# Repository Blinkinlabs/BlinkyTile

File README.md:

BlinkyTile: Build Your Own Dynamic Light Sculptures
==========

BlinkyTile is a very special type of pentagonal tile, designed to let you create your own custom light sculptures.

This is the source repository for the BlinkyTile design and software. For more information, head to:

http://blinkytile.com/

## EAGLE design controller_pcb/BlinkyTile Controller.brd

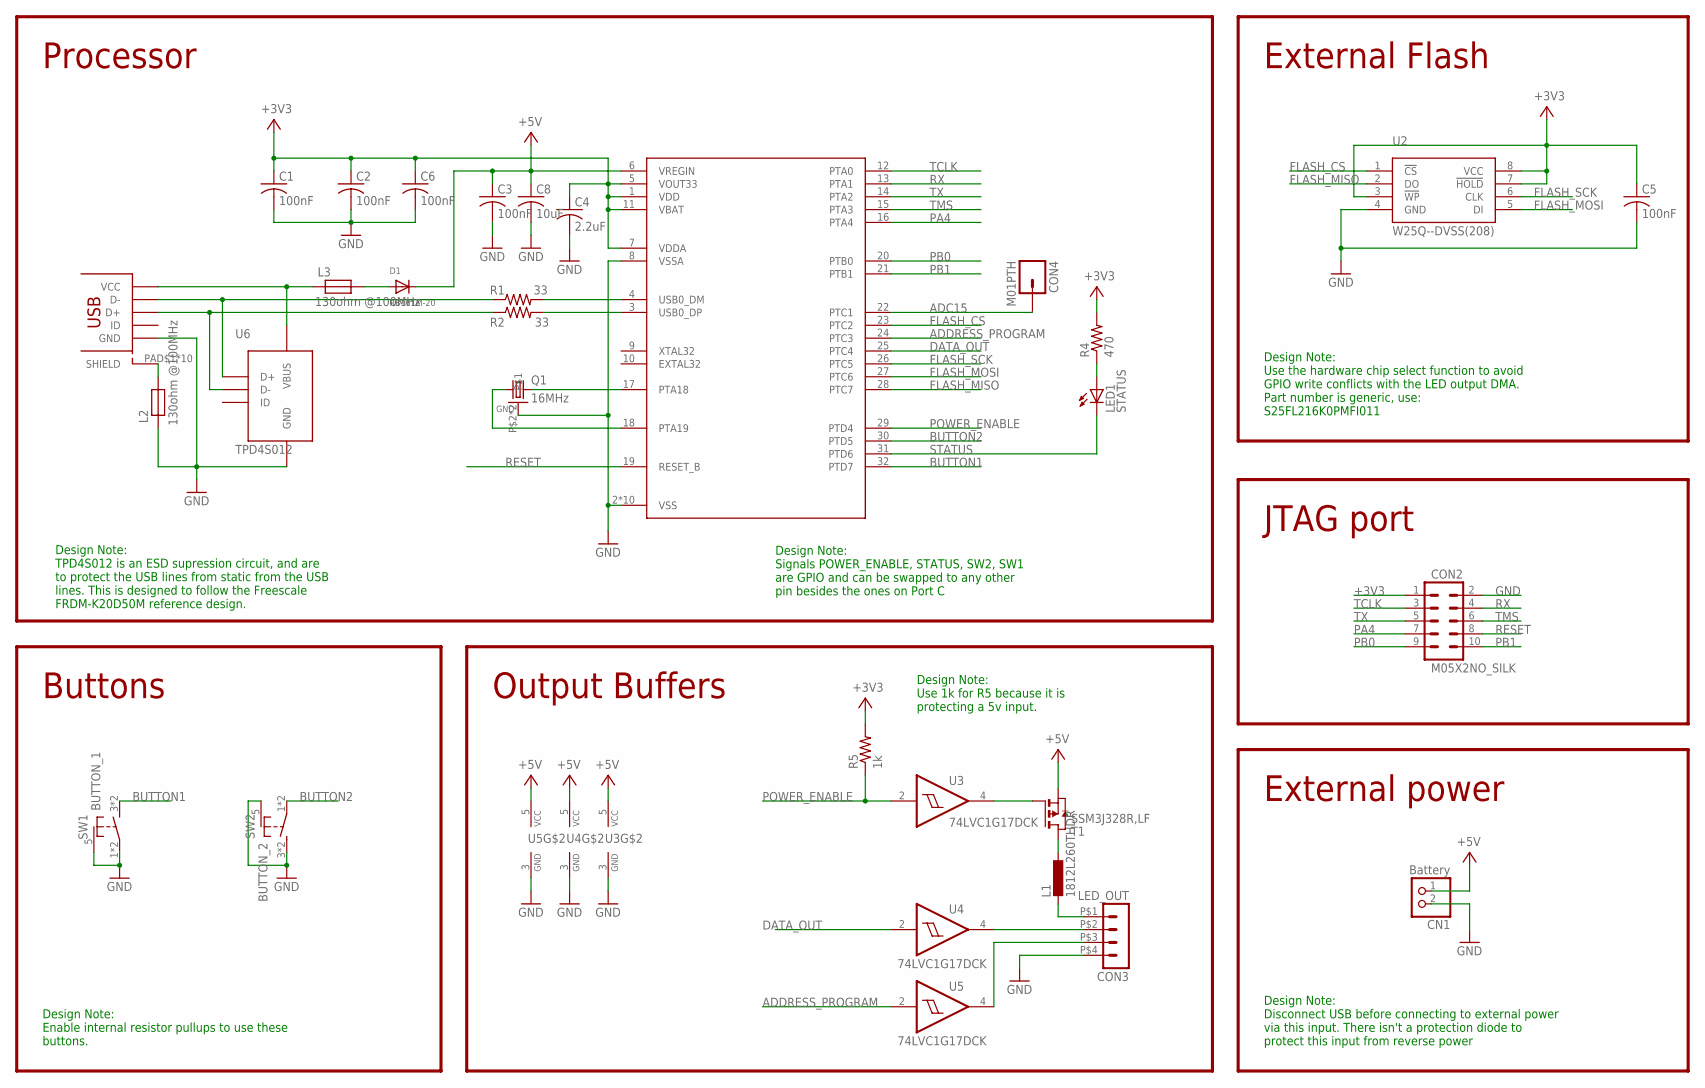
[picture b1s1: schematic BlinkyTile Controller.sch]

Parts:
C1, C2, C3, C5, C6: 100nF; C0402
C4: 2.2uF; C0402
C8: 10uF; C0805K
CN1: Battery; JST-PH-2-THM-RA
CON1: USB_MICROSMT+THRUHULE; USB_MICRO_THRUHOLE
CON2: M05X2NO_SILK; 2X5_NOSILK
CON3: LED_OUT; DUPONT-4P
CON4: M01PTH; 1X01
D1: RB161M-20; SOD-123
L1: 1812L260THDR; L1812
L2, L3: 130ohm @100MHz; 0805
LED1: STATUS; CHIPLED_0805
Q1: 16MHz; CRSYTAL_2520
R1, R2: 33; R0402
R4: 470; R0402
R5: 1k; R0402
SW1: BUTTON_1; TD-07XB
SW2: BUTTON_2; TD-07XB
T1: SSM3J328R,LF; SOT-23
U1: MK20D--VFM5; QFN32_5X5_LONGLEADS
U2: W25Q--DVSS(208); SOIC8-208
U3, U4, U5: 74LVC1G17DCK; SC70-5
U6: TPD4S012; R-PUSON-N6

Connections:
+3V3: C1.1, C2.1, C4.1, C5.1, C6.1, CON2.1, R4.2, R5.2, U1.1 (VDD), U1.5 (VOUT33), U1.7 (VDDA), U1.11 (VBAT), U2.3 (!WP), U2.7 (!HOLD), U2.8 (VCC)
+5V: C3.1, C8.1, CN1.1 (2), D1.C, T1.2 (S), U1.6 (VREGIN), U3.5 (VCC), U4.5 (VCC), U5.5 (VCC)
ADC15: CON4.1, U1.22 (PTC1)
ADDRESS_PROGRAM: U1.24 (PTC3), U5.2 (I)
BUTTON1: SW1.3 (S), SW1.4 (S), U1.32 (PTD7)
BUTTON2: SW2.1, SW2.2, U1.30 (PTD5)
DATA_OUT: U1.25 (PTC4), U4.2 (I)
FLASH_CS: U1.23 (PTC2), U2.1 (!CS)
FLASH_MISO: U1.28 (PTC7), U2.2 (DO)
FLASH_MOSI: U1.27 (PTC6), U2.5 (DI)
FLASH_SCK: U1.26 (PTC5), U2.6 (CLK)
GND: C1.2, C2.2, C3.2, C4.2, C5.2, C6.2, C8.2, CN1.2 (1), CON1.PIN$5 (GND), CON2.2, CON3.P$4 (4), L2.2, Q1.P$2, Q1.P$4, SW1.1, SW1.2, SW1.5 (SHIELD), SW2.3 (S), SW2.4 (S), SW2.5 (SHIELD), U1.2 (VSS), U1.8 (VSSA), U1.PAD@1 (VSS), U1.PAD@2 (VSS), U1.PAD@3 (VSS), U1.PAD@4 (VSS), U1.PAD@5 (VSS), U1.PAD@6 (VSS), U1.PAD@9 (VSS), U1.PAD@10 (VSS), U1.PAD@11 (VSS), U2.4 (GND), U3.3 (GND), U4.3 (GND), U5.3 (GND), U6.P$4 (GND)
LED_DATA: CON3.P$2 (2), U4.4 (O)
unnamed: Q1.P$1 (1), U1.18 (PTA19)
unnamed: Q1.P$3 (2), U1.17 (PTA18)
unnamed: CON1.PIN$1 (VCC), L3.2, U6.P$6 (VBUS)
unnamed: CON3.P$3 (3), U5.4 (O)
unnamed: L1.1, T1.1 (D)
unnamed: T1.3 (G), U3.4 (O)
unnamed: CON1.PIN$2 (D-), R1.1, U6.P$1 (D+)
unnamed: CON3.P$1 (1), L1.2
unnamed: D1.A, L3.1
unnamed: CON1.PIN$3 (D+), R2.1, U6.P$2 (D-)
unnamed: R1.2, U1.4 (USB0_DM)
unnamed: R2.2, U1.3 (USB0_DP)
unnamed: LED1.A, R4.1
PA4: CON2.7, U1.16 (PTA4)
PB0: CON2.9, U1.20 (PTB0)
PB1: CON2.10, U1.21 (PTB1)
POWER_ENABLE: R5.1, U1.29 (PTD4), U3.2 (I)
RESET: CON2.8, U1.19 (RESET_B)
RX: CON2.4, U1.13 (PTA1)
SHIELD: CON1.PAD$1 (SHIELD), CON1.PAD$2 (SHIELD), CON1.PAD$3 (SHIELD), CON1.PAD$4 (SHIELD), CON1.PAD$5 (SHIELD), CON1.PAD$6 (SHIELD), CON1.PAD$7 (SHIELD), CON1.PAD$8 (SHIELD), CON1.PAD$9 (SHIELD), CON1.PAD$10 (SHIELD), L2.1
STATUS: LED1.C, U1.31 (PTD6)
TCLK: CON2.3, U1.12 (PTA0)
TMS: CON2.6, U1.15 (PTA3)
TX: CON2.5, U1.14 (PTA2)

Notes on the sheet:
Processor
External Flash
Buttons
Design Note: Signals POWER_ENABLE, STATUS, SW2, SW1 are GPIO and can be swapped to any other pin besides the ones on Port C
Design Note: TPD4S012 is an ESD supression circuit, and are to protect the USB lines from static from the USB lines. This is designed to follow the Freescale FRDM-K20D50M reference design.
Output Buffers
JTAG port
External power
Design Note: Use 1k for R5 because it is protecting a 5v input.
Design Note: Use the hardware chip select function to avoid GPIO write conflicts with the LED output DMA. Part number is generic, use: S25FL216K0PMFI011
Design Note: Disconnect USB before connecting to external power via this input. There isn't a protection diode to protect this input from reverse power
Design Note: Enable internal resistor pullups to use these buttons.

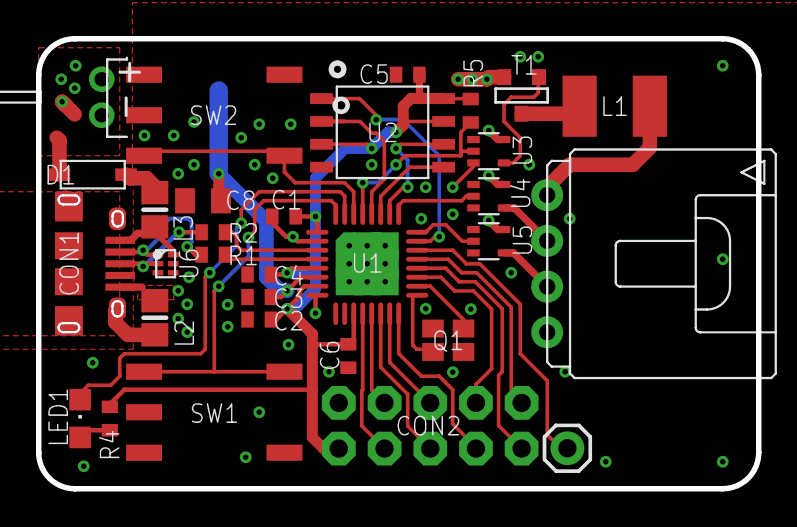
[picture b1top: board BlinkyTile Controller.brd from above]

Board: 2 copper layers, 40.0 x 25.0 mm, 31 parts (0 on the bottom side), 37 nets.

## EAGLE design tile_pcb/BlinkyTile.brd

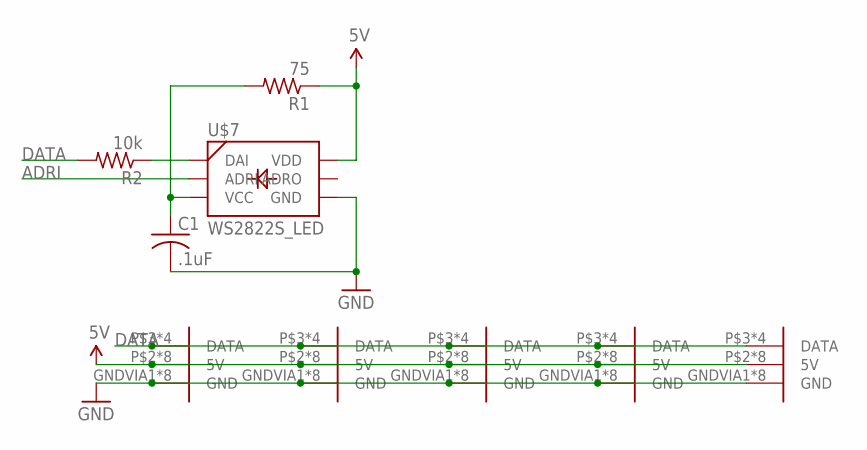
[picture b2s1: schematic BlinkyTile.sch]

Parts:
C1: .1uF; C0603
R1: 75; R0603
R2: 10k; R0603
U$2, U$3, U$4, U$5, U$6: D_EDGEMOD; D_EDGE_SLOT_MOD
U$7: WS2822S_LED

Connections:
5V: R1.1, U$2.P$2 (5V), U$2.P$4 (5V), U$2.P$7 (5V), U$2.P$9 (5V), U$2.PWRVIA1 (5V), U$2.PWRVIA3 (5V), U$2.PWRVIA4 (5V), U$2.PWRVIA6 (5V), U$3.P$2 (5V), U$3.P$4 (5V), U$3.P$7 (5V), U$3.P$9 (5V), U$3.PWRVIA1 (5V), U$3.PWRVIA3 (5V), U$3.PWRVIA4 (5V), U$3.PWRVIA6 (5V), U$4.P$2 (5V), U$4.P$4 (5V), U$4.P$7 (5V), U$4.P$9 (5V), U$4.PWRVIA1 (5V), U$4.PWRVIA3 (5V), U$4.PWRVIA4 (5V), U$4.PWRVIA6 (5V), U$5.P$2 (5V), U$5.P$4 (5V), U$5.P$7 (5V), U$5.P$9 (5V), U$5.PWRVIA1 (5V), U$5.PWRVIA3 (5V), U$5.PWRVIA4 (5V), U$5.PWRVIA6 (5V), U$6.P$2 (5V), U$6.P$4 (5V), U$6.P$7 (5V), U$6.P$9 (5V), U$6.PWRVIA1 (5V), U$6.PWRVIA3 (5V), U$6.PWRVIA4 (5V), U$6.PWRVIA6 (5V), U$7.6 (VDD)
ADRI: U$7.2 (ADRI)
DATA: R2.2, U$2.P$3 (DATA), U$2.P$8 (DATA), U$2.SIGVIA1 (DATA), U$2.SIGVIA3 (DATA), U$3.P$3 (DATA), U$3.P$8 (DATA), U$3.SIGVIA1 (DATA), U$3.SIGVIA3 (DATA), U$4.P$3 (DATA), U$4.P$8 (DATA), U$4.SIGVIA1 (DATA), U$4.SIGVIA3 (DATA), U$5.P$3 (DATA), U$5.P$8 (DATA), U$5.SIGVIA1 (DATA), U$5.SIGVIA3 (DATA), U$6.P$3 (DATA), U$6.P$8 (DATA), U$6.SIGVIA1 (DATA), U$6.SIGVIA3 (DATA)
GND: C1.2, U$2.GNDVIA1 (GND), U$2.GNDVIA3 (GND), U$2.GNDVIA4 (GND), U$2.GNDVIA6 (GND), U$2.P$1 (GND), U$2.P$5 (GND), U$2.P$6 (GND), U$2.P$10 (GND), U$3.GNDVIA1 (GND), U$3.GNDVIA3 (GND), U$3.GNDVIA4 (GND), U$3.GNDVIA6 (GND), U$3.P$1 (GND), U$3.P$5 (GND), U$3.P$6 (GND), U$3.P$10 (GND), U$4.GNDVIA1 (GND), U$4.GNDVIA3 (GND), U$4.GNDVIA4 (GND), U$4.GNDVIA6 (GND), U$4.P$1 (GND), U$4.P$5 (GND), U$4.P$6 (GND), U$4.P$10 (GND), U$5.GNDVIA1 (GND), U$5.GNDVIA3 (GND), U$5.GNDVIA4 (GND), U$5.GNDVIA6 (GND), U$5.P$1 (GND), U$5.P$5 (GND), U$5.P$6 (GND), U$5.P$10 (GND), U$6.GNDVIA1 (GND), U$6.GNDVIA3 (GND), U$6.GNDVIA4 (GND), U$6.GNDVIA6 (GND), U$6.P$1 (GND), U$6.P$5 (GND), U$6.P$6 (GND), U$6.P$10 (GND), U$7.4 (GND)
unnamed: C1.1, R1.2, U$7.3 (VCC)
unnamed: R2.1, U$7.1 (DAI)

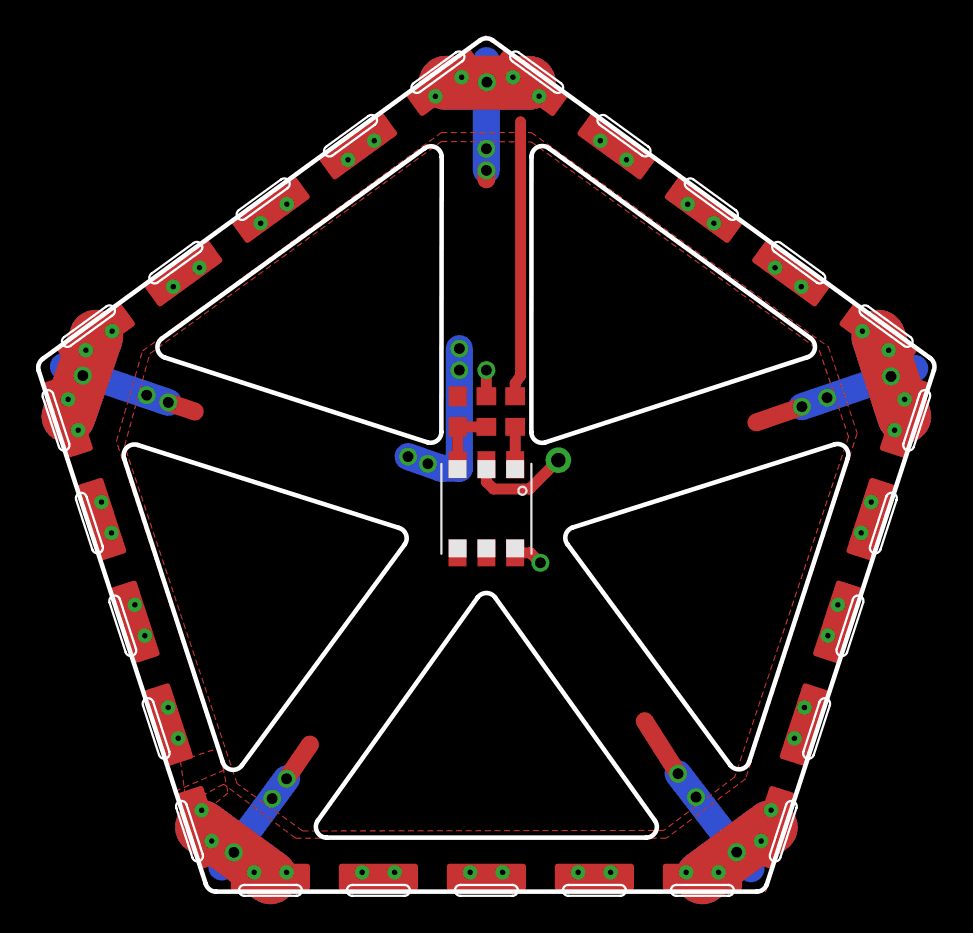
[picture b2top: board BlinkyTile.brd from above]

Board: 2 copper layers, 49.8 x 47.6 mm, 9 parts (0 on the bottom side), 5 nets.

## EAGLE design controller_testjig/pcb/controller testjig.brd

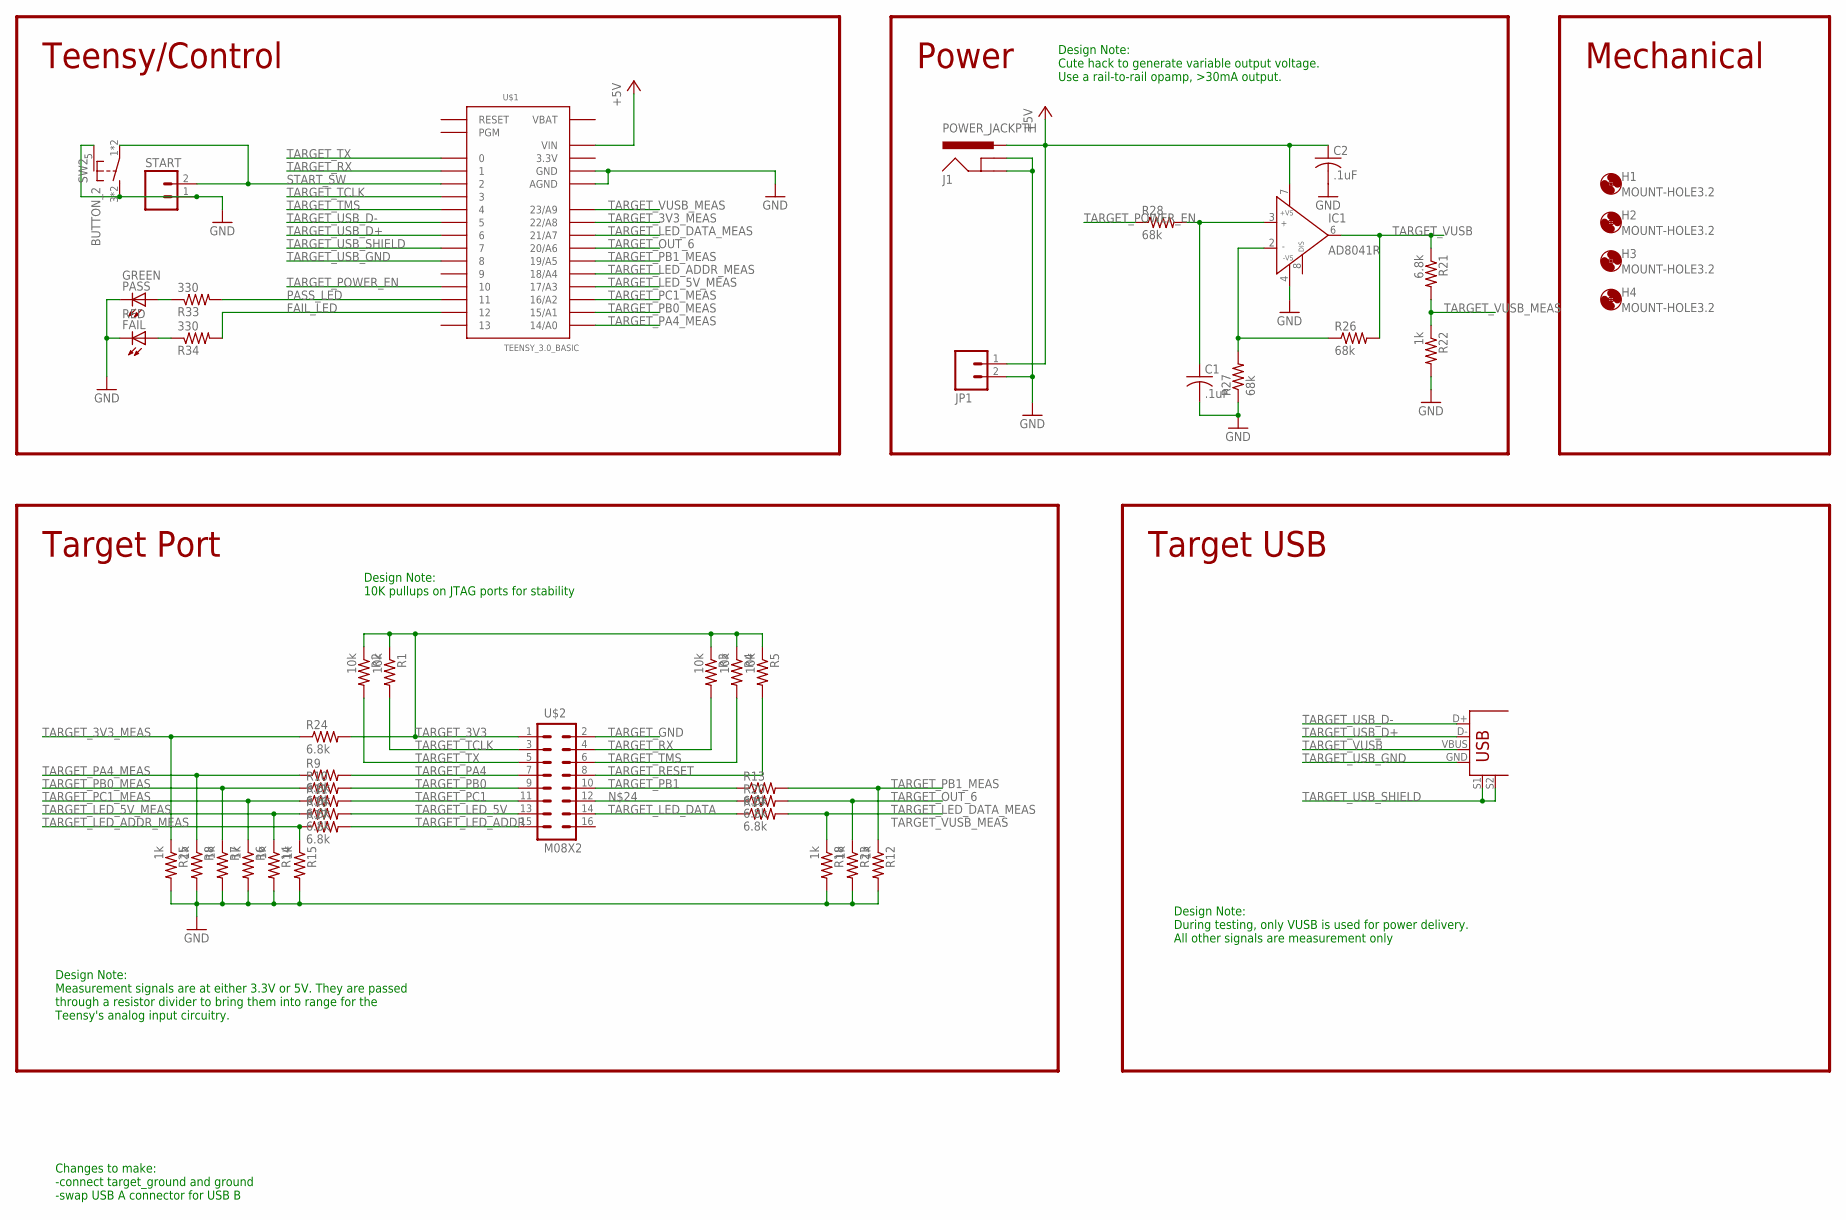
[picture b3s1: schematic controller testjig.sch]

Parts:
C1, C2: .1uF; C0603
FAIL: RED; LED5MM
H1, H2, H3, H4: MOUNT-HOLE3.2; 3,2
IC1: AD8041R; SO8
J1: POWER_JACKPTH; POWER_JACK_PTH
JP1: M023.5MM; SCREWTERMINAL-3.5MM-2
PASS: GREEN; LED5MM
R1, R2, R3, R4, R5: 10k; R0603
R6, R7, R8, R12, R14, R15, R18, R22, R23, R25: 1k; R0603
R9, R10, R11, R13, R16, R17, R19, R20, R21, R24: 6.8k; R0603
R26, R27, R28: 68k; R0603
R33, R34: 330; R0603
START: M02; 02P
SW2: BUTTON_2; TD-07XB
U$1: TEENSY_3.0_BASIC
U$2: M08X2; 2X8
U$3: USB+SHIELD; USB-B-PTH

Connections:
3.3V: U$1.3.3V, U$1.3.3V1 (3.3V)
+5V: C2.1, IC1.7 (+VS), J1.PWR, JP1.1, U$1.VIN
FAIL_LED: R34.2, U$1.12
GND: C1.2, C2.2, FAIL.K (C), IC1.4 (-VS), J1.GND, J1.GNDBREAK, JP1.2, PASS.K (C), R6.2, R7.2, R8.2, R12.2, R14.2, R15.2, R18.2, R22.2, R23.2, R25.2, R27.1, START.1, SW2.3 (S), SW2.4 (S), SW2.5 (SHIELD), U$1.AGND, U$1.GND, U$1.GND1 (GND)
GOOD: PASS.A, R33.1
unnamed: IC1.2 (IN-), R26.1, R27.2
unnamed: C1.1, IC1.3 (IN+), R28.2
unnamed: R20.1, U$2.12
unnamed: FAIL.A, R34.1
PASS_LED: R33.2, U$1.11
START_SW: START.2, SW2.1, SW2.2, U$1.2
TARGET_3V3: R1.1, R2.1, R3.1, R4.1, R5.1, R24.2, U$2.1
TARGET_3V3_MEAS: R24.1, R25.1, U$1.22/A8
TARGET_GND: U$2.2
TARGET_LED_5V: R16.2, U$2.13
TARGET_LED_5V_MEAS: R14.1, R16.1, U$1.17/A3
TARGET_LED_ADDR: R17.2, U$2.15
TARGET_LED_ADDR_MEAS: R15.1, R17.1, U$1.18/A4
TARGET_LED_DATA: R19.1, U$2.14
TARGET_LED_DATA_MEAS: R18.1, R19.2, U$1.21/A7
TARGET_OUT_6: R20.2, R23.1, U$1.20/A6
TARGET_PA4: R9.2, U$2.7
TARGET_PA4_MEAS: R8.1, R9.1, U$1.14/A0
TARGET_PB0: R10.2, U$2.9
TARGET_PB0_MEAS: R7.1, R10.1, U$1.15/A1
TARGET_PB1: R13.1, U$2.10
TARGET_PB1_MEAS: R12.1, R13.2, U$1.19/A5
TARGET_PC1: R11.2, U$2.11
TARGET_PC1_MEAS: R6.1, R11.1, U$1.16/A2
TARGET_POWER_EN: R28.1, U$1.10
TARGET_RESET: R5.2, U$2.8
TARGET_RX: R3.2, U$1.1, U$2.4
TARGET_TCLK: R1.2, U$1.3, U$2.3
TARGET_TMS: R4.2, U$1.4, U$2.6
TARGET_TX: R2.2, U$1.0, U$2.5
TARGET_USB_D+: U$1.5, U$3.D+
TARGET_USB_D-: U$1.6, U$3.D-
TARGET_USB_GND: U$1.8, U$3.GND
TARGET_USB_SHIELD: U$1.7, U$3.S1, U$3.S2
TARGET_VUSB: IC1.6 (OUT), R21.1, R26.2, U$3.VBUS
TARGET_VUSB_MEAS: R21.2, R22.1, U$1.23/A9
VBAT: U$1.VBAT

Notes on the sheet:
Teensy/Control
Target Port
Design Note: Measurement signals are at either 3.3V or 5V. They are passed through a resistor divider to bring them into range for the Teensy's analog input circuitry.
Design Note: 10K pullups on JTAG ports for stability
Mechanical
Target USB
Power
Design Note: During testing, only VUSB is used for power delivery. All other signals are measurement only
Design Note: Cute hack to generate variable output voltage. Use a rail-to-rail opamp, >30mA output.
Changes to make: -connect target_ground and ground -swap USB A connector for USB B

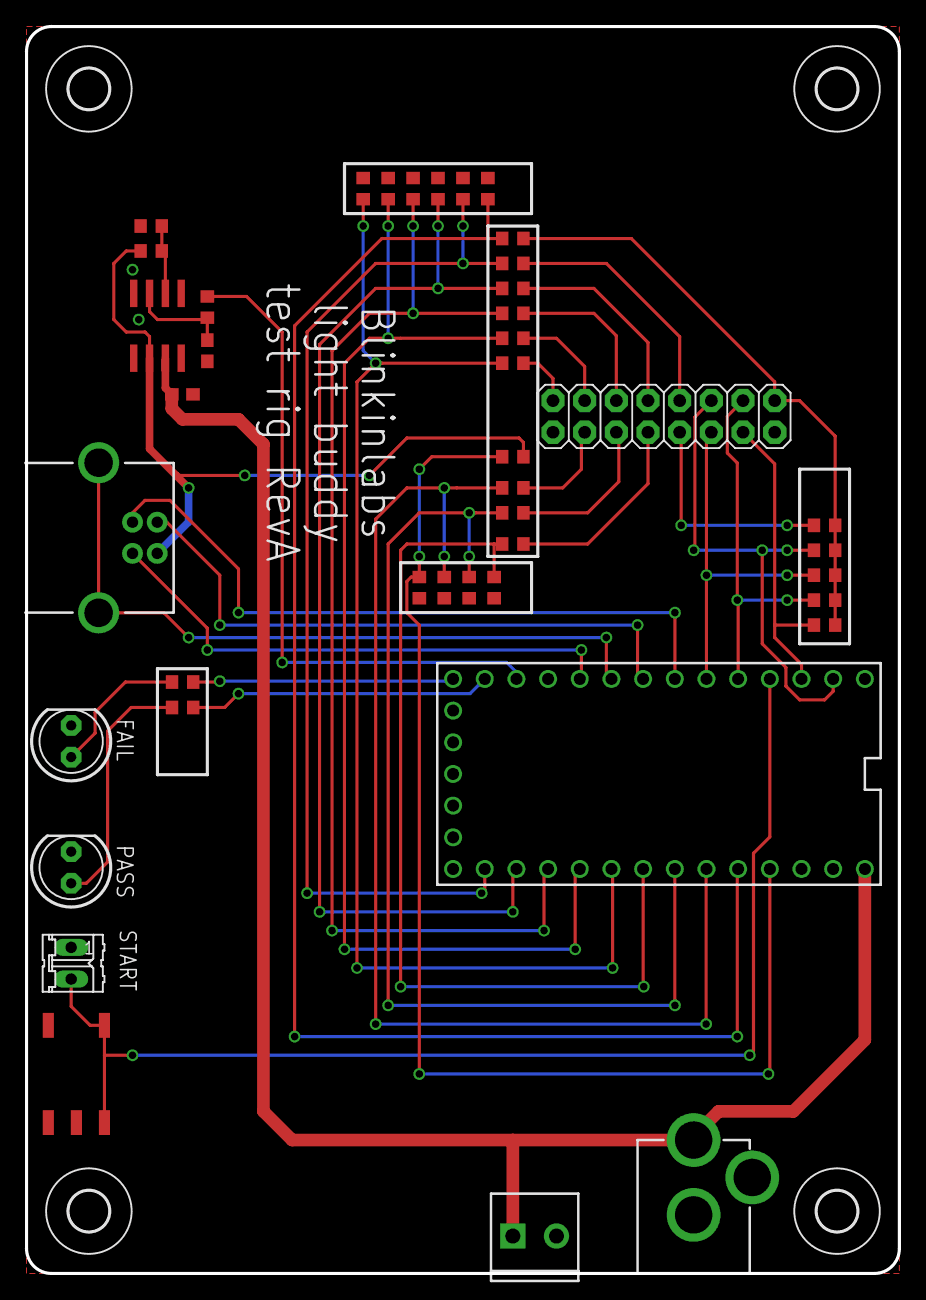
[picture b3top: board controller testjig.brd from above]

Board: 2 copper layers, 70.0 x 100.0 mm, 46 parts (0 on the bottom side), 40 nets.

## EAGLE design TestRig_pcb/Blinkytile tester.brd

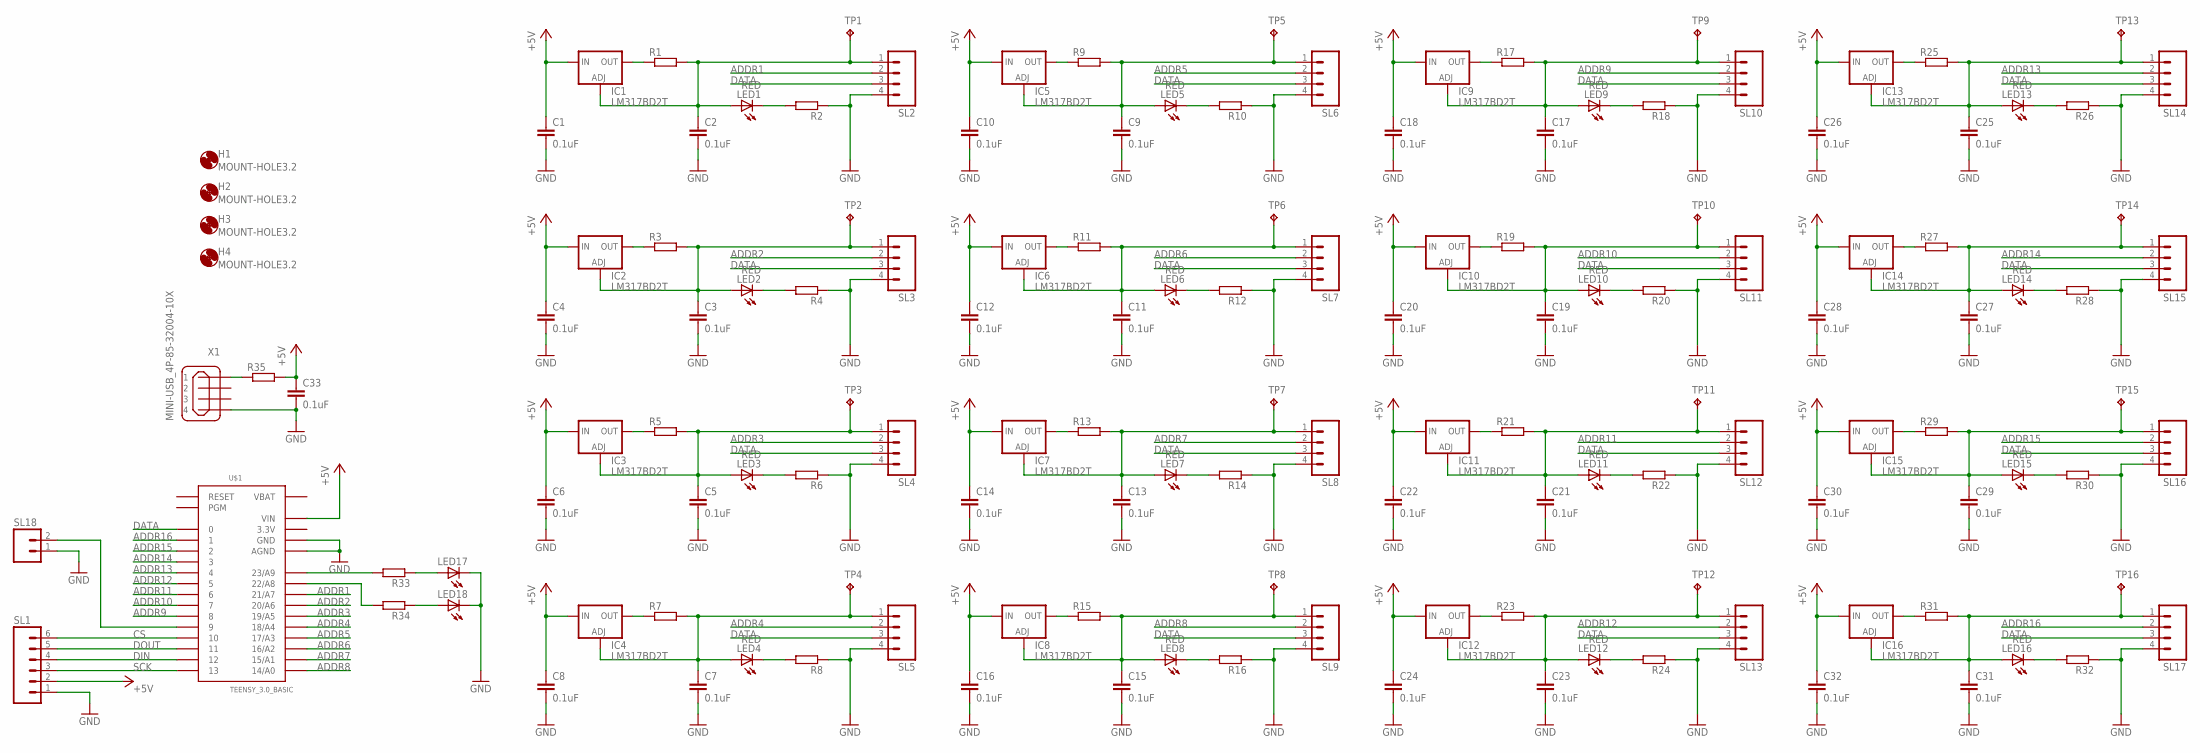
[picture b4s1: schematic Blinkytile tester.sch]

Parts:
C1, C2, C3, C4, C5, C6, C7, C8, C9, C10, C11, C12, C13, C14, C15, C16, C17, C18, C19, C20, C21, C22, C23, C24, C25, C26, C27, C28, C29, C30, C31, C32, C33: 0.1uF; C0805
H1, H2, H3, H4: MOUNT-HOLE3.2; 3,2
IC1, IC2, IC3, IC4, IC5, IC6, IC7, IC8, IC9, IC10, IC11, IC12, IC13, IC14, IC15, IC16: LM317BD2T; D2PACK
LED1, LED2, LED3, LED4, LED5, LED6, LED7, LED8, LED9, LED10, LED11, LED12, LED13, LED14, LED15, LED16: RED; LED5MM
LED17, LED18: LED5MM
R1, R2, R3, R4, R5, R6, R7, R8, R9, R10, R11, R12, R13, R14, R15, R16, R17, R18, R19, R20, R21, R22, R23, R24, R25, R26, R27, R28, R29, R30, R31, R32, R33, R34, R35: R-EU_M0805; M0805
SL1: M06; 06P
SL2, SL3, SL4, SL5, SL6, SL7, SL8, SL9, SL10, SL11, SL12, SL13, SL14, SL15, SL16, SL17: M04; 04P
SL18: M02; 02P
TP1, TP2, TP3, TP4, TP5, TP6, TP7, TP8, TP9, TP10, TP11, TP12, TP13, TP14, TP15, TP16: TPPAD1-13Y; P1-13Y
U$1: TEENSY_3.0_BASIC
X1: MINI-USB_4P-85-32004-10X; 85-32004-10X

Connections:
3.3V: U$1.3.3V, U$1.3.3V1 (3.3V)
+5V: C1.1, C4.1, C6.1, C8.1, C10.1, C12.1, C14.1, C16.1, C18.1, C20.1, C22.1, C24.1, C26.1, C28.1, C30.1, C32.1, C33.1, IC1.3 (IN), IC2.3 (IN), IC3.3 (IN), IC4.3 (IN), IC5.3 (IN), IC6.3 (IN), IC7.3 (IN), IC8.3 (IN), IC9.3 (IN), IC10.3 (IN), IC11.3 (IN), IC12.3 (IN), IC13.3 (IN), IC14.3 (IN), IC15.3 (IN), IC16.3 (IN), R35.2, SL1.2, U$1.VIN
ADDR1: SL2.2, U$1.21/A7
ADDR2: SL3.2, U$1.20/A6
ADDR3: SL4.2, U$1.19/A5
ADDR4: SL5.2, U$1.18/A4
ADDR5: SL6.2, U$1.17/A3
ADDR6: SL7.2, U$1.16/A2
ADDR7: SL8.2, U$1.15/A1
ADDR8: SL9.2, U$1.14/A0
ADDR9: SL10.2, U$1.8
ADDR10: SL11.2, U$1.7
ADDR11: SL12.2, U$1.6
ADDR12: SL13.2, U$1.5
ADDR13: SL14.2, U$1.4
ADDR14: SL15.2, U$1.3
ADDR15: SL16.2, U$1.2
ADDR16: SL17.2, U$1.1
CS: SL1.6, U$1.10
DATA: SL2.3, SL3.3, SL4.3, SL5.3, SL6.3, SL7.3, SL8.3, SL9.3, SL10.3, SL11.3, SL12.3, SL13.3, SL14.3, SL15.3, SL16.3, SL17.3, U$1.0
DIN: SL1.4, U$1.12
DOUT: SL1.5, U$1.11
GND: C1.2, C2.2, C3.2, C4.2, C5.2, C6.2, C7.2, C8.2, C9.2, C10.2, C11.2, C12.2, C13.2, C14.2, C15.2, C16.2, C17.2, C18.2, C19.2, C20.2, C21.2, C22.2, C23.2, C24.2, C25.2, C26.2, C27.2, C28.2, C29.2, C30.2, C31.2, C32.2, C33.2, LED17.K (C), LED18.K (C), R2.1, R4.1, R6.1, R8.1, R10.1, R12.1, R14.1, R16.1, R18.1, R20.1, R22.1, R24.1, R26.1, R28.1, R30.1, R32.1, SL1.1, SL2.4, SL3.4, SL4.4, SL5.4, SL6.4, SL7.4, SL8.4, SL9.4, SL10.4, SL11.4, SL12.4, SL13.4, SL14.4, SL15.4, SL16.4, SL17.4, SL18.1, U$1.AGND, U$1.GND, U$1.GND1 (GND), X1.4
unnamed: IC1.2 (OUT), R1.1
unnamed: C2.1, IC1.1 (ADJ), LED1.A, R1.2, SL2.1, TP1.TP
unnamed: IC2.2 (OUT), R3.1
unnamed: C3.1, IC2.1 (ADJ), LED2.A, R3.2, SL3.1, TP2.TP
unnamed: LED1.K (C), R2.2
unnamed: LED2.K (C), R4.2
unnamed: IC3.2 (OUT), R5.1
unnamed: C5.1, IC3.1 (ADJ), LED3.A, R5.2, SL4.1, TP3.TP
unnamed: LED3.K (C), R6.2
unnamed: IC4.2 (OUT), R7.1
unnamed: C7.1, IC4.1 (ADJ), LED4.A, R7.2, SL5.1, TP4.TP
unnamed: LED4.K (C), R8.2
unnamed: IC5.2 (OUT), R9.1
unnamed: C9.1, IC5.1 (ADJ), LED5.A, R9.2, SL6.1, TP5.TP
unnamed: LED5.K (C), R10.2
unnamed: IC6.2 (OUT), R11.1
unnamed: C11.1, IC6.1 (ADJ), LED6.A, R11.2, SL7.1, TP6.TP
unnamed: LED6.K (C), R12.2
unnamed: IC7.2 (OUT), R13.1
unnamed: C13.1, IC7.1 (ADJ), LED7.A, R13.2, SL8.1, TP7.TP
unnamed: LED7.K (C), R14.2
unnamed: IC8.2 (OUT), R15.1
unnamed: C15.1, IC8.1 (ADJ), LED8.A, R15.2, SL9.1, TP8.TP
unnamed: LED8.K (C), R16.2
unnamed: IC9.2 (OUT), R17.1
unnamed: C17.1, IC9.1 (ADJ), LED9.A, R17.2, SL10.1, TP9.TP
unnamed: LED9.K (C), R18.2
unnamed: IC10.2 (OUT), R19.1
unnamed: C19.1, IC10.1 (ADJ), LED10.A, R19.2, SL11.1, TP10.TP
unnamed: LED10.K (C), R20.2
unnamed: IC11.2 (OUT), R21.1
unnamed: C21.1, IC11.1 (ADJ), LED11.A, R21.2, SL12.1, TP11.TP
unnamed: LED11.K (C), R22.2
unnamed: IC12.2 (OUT), R23.1
unnamed: C23.1, IC12.1 (ADJ), LED12.A, R23.2, SL13.1, TP12.TP
unnamed: LED12.K (C), R24.2
unnamed: IC13.2 (OUT), R25.1
unnamed: C25.1, IC13.1 (ADJ), LED13.A, R25.2, SL14.1, TP13.TP
unnamed: LED13.K (C), R26.2
unnamed: IC14.2 (OUT), R27.1
unnamed: C27.1, IC14.1 (ADJ), LED14.A, R27.2, SL15.1, TP14.TP
unnamed: LED14.K (C), R28.2
unnamed: IC15.2 (OUT), R29.1
unnamed: C29.1, IC15.1 (ADJ), LED15.A, R29.2, SL16.1, TP15.TP
unnamed: LED15.K (C), R30.2
unnamed: IC16.2 (OUT), R31.1
unnamed: C31.1, IC16.1 (ADJ), LED16.A, R31.2, SL17.1, TP16.TP
unnamed: LED16.K (C), R32.2
unnamed: R33.2, U$1.23/A9
unnamed: R34.2, U$1.22/A8
unnamed: LED17.A, R33.1
unnamed: LED18.A, R34.1
unnamed: R35.1, X1.1
unnamed: SL18.2, U$1.9
SCK: SL1.3, U$1.13
VBAT: U$1.VBAT

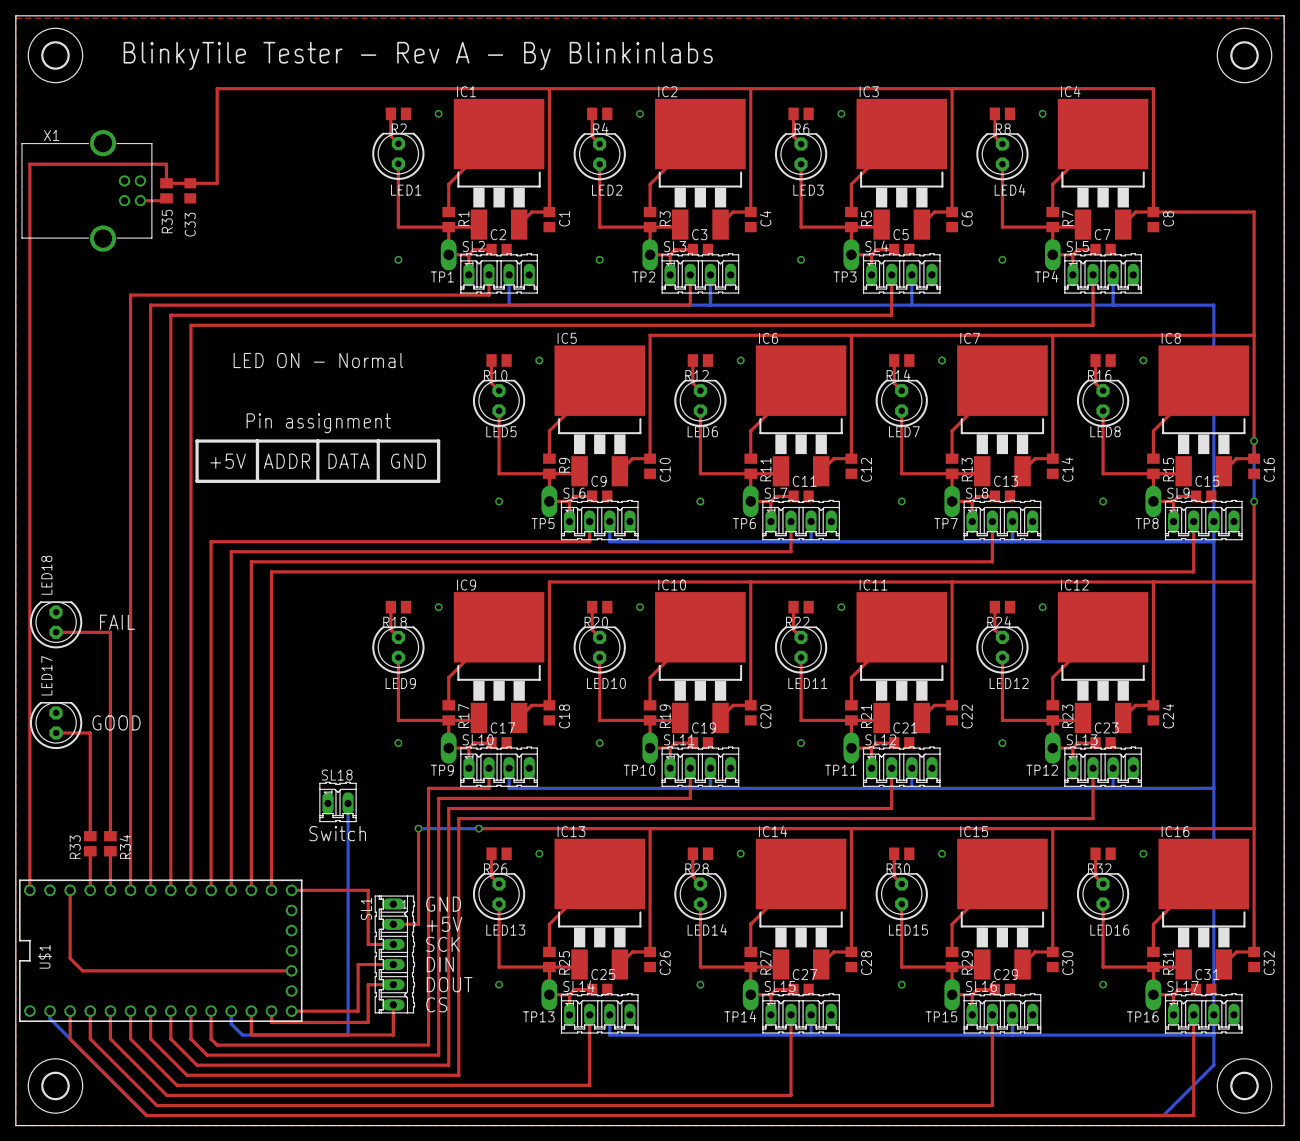
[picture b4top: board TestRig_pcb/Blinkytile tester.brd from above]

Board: 2 copper layers, 160.0 x 140.0 mm, 142 parts (0 on the bottom side), 78 nets.

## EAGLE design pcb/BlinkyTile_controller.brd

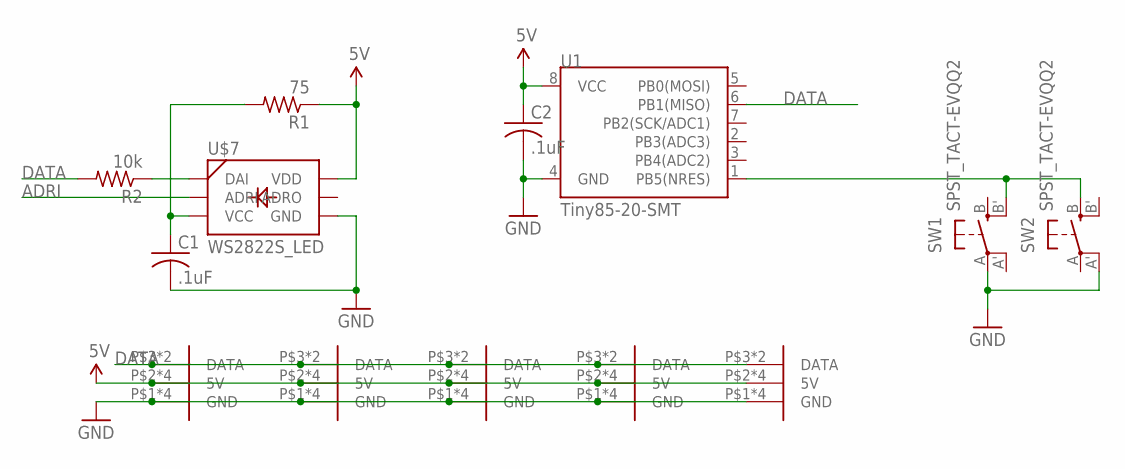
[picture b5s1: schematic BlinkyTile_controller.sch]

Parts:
C1, C2: .1uF; C0603
R1: 75; R0603
R2: 10k; R0603
SW1, SW2: SPST_TACT-EVQQ2; EVQ-Q2
U1: Tiny85-20-SMT; SO08-EIAJ
U$2, U$3, U$4, U$5, U$6: D_EDGESLOT; D_EDGE_SLOT
U$7: WS2822S_LED

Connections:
5V: C2.1, R1.1, U1.8 (VCC), U$2.P$2 (5V), U$2.P$4 (5V), U$2.P$7 (5V), U$2.P$9 (5V), U$3.P$2 (5V), U$3.P$4 (5V), U$3.P$7 (5V), U$3.P$9 (5V), U$4.P$2 (5V), U$4.P$4 (5V), U$4.P$7 (5V), U$4.P$9 (5V), U$5.P$2 (5V), U$5.P$4 (5V), U$5.P$7 (5V), U$5.P$9 (5V), U$6.P$2 (5V), U$6.P$4 (5V), U$6.P$7 (5V), U$6.P$9 (5V), U$7.6 (VDD)
ADRI: U$7.2 (ADRI)
DATA: R2.2, U1.6 (PB1(MISO)), U$2.P$3 (DATA), U$2.P$8 (DATA), U$3.P$3 (DATA), U$3.P$8 (DATA), U$4.P$3 (DATA), U$4.P$8 (DATA), U$5.P$3 (DATA), U$5.P$8 (DATA), U$6.P$3 (DATA), U$6.P$8 (DATA)
GND: C1.2, C2.2, SW1.A, SW2.A' (P1), U1.4 (GND), U$2.P$1 (GND), U$2.P$5 (GND), U$2.P$6 (GND), U$2.P$10 (GND), U$3.P$1 (GND), U$3.P$5 (GND), U$3.P$6 (GND), U$3.P$10 (GND), U$4.P$1 (GND), U$4.P$5 (GND), U$4.P$6 (GND), U$4.P$10 (GND), U$5.P$1 (GND), U$5.P$5 (GND), U$5.P$6 (GND), U$5.P$10 (GND), U$6.P$1 (GND), U$6.P$5 (GND), U$6.P$6 (GND), U$6.P$10 (GND), U$7.4 (GND)
unnamed: C1.1, R1.2, U$7.3 (VCC)
unnamed: R2.1, U$7.1 (DAI)
unnamed: SW1.B' (S1), SW2.B (S), U1.1 (PB5(NRES))

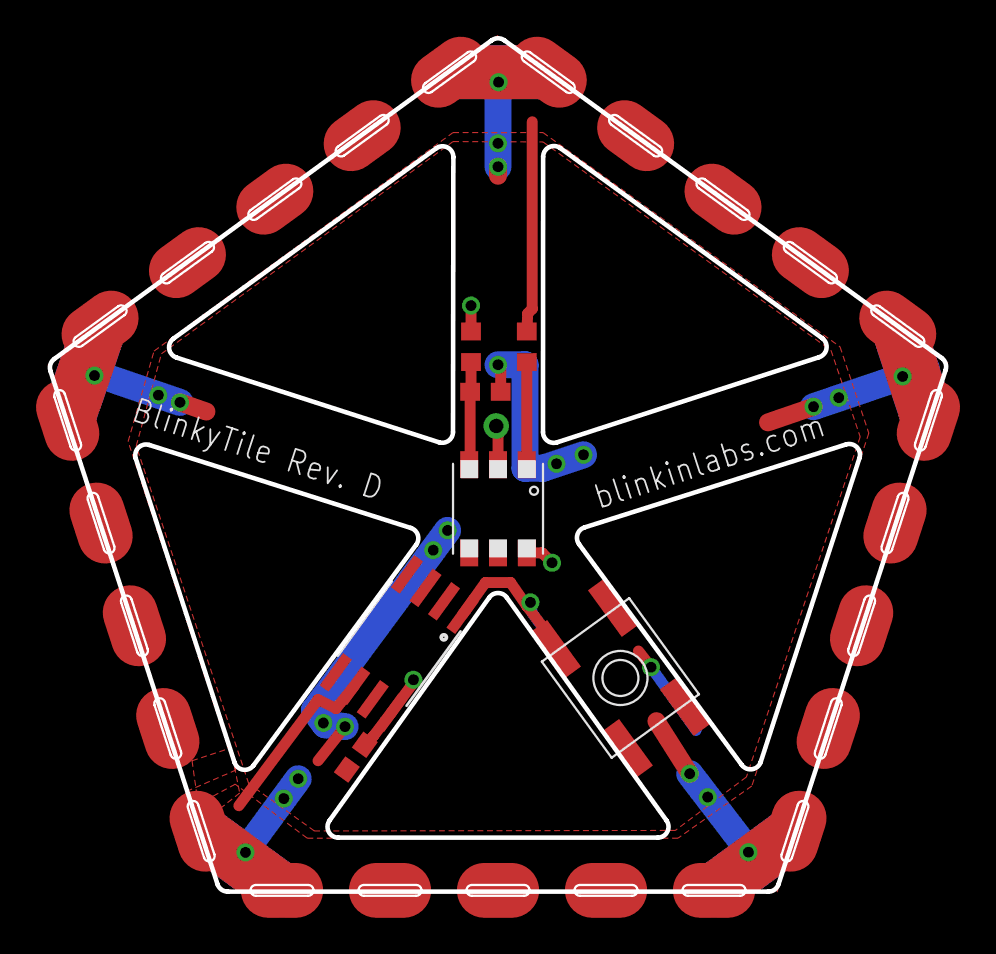
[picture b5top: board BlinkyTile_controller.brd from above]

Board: 2 copper layers, 49.8 x 47.6 mm, 13 parts (1 on the bottom side), 6 nets.

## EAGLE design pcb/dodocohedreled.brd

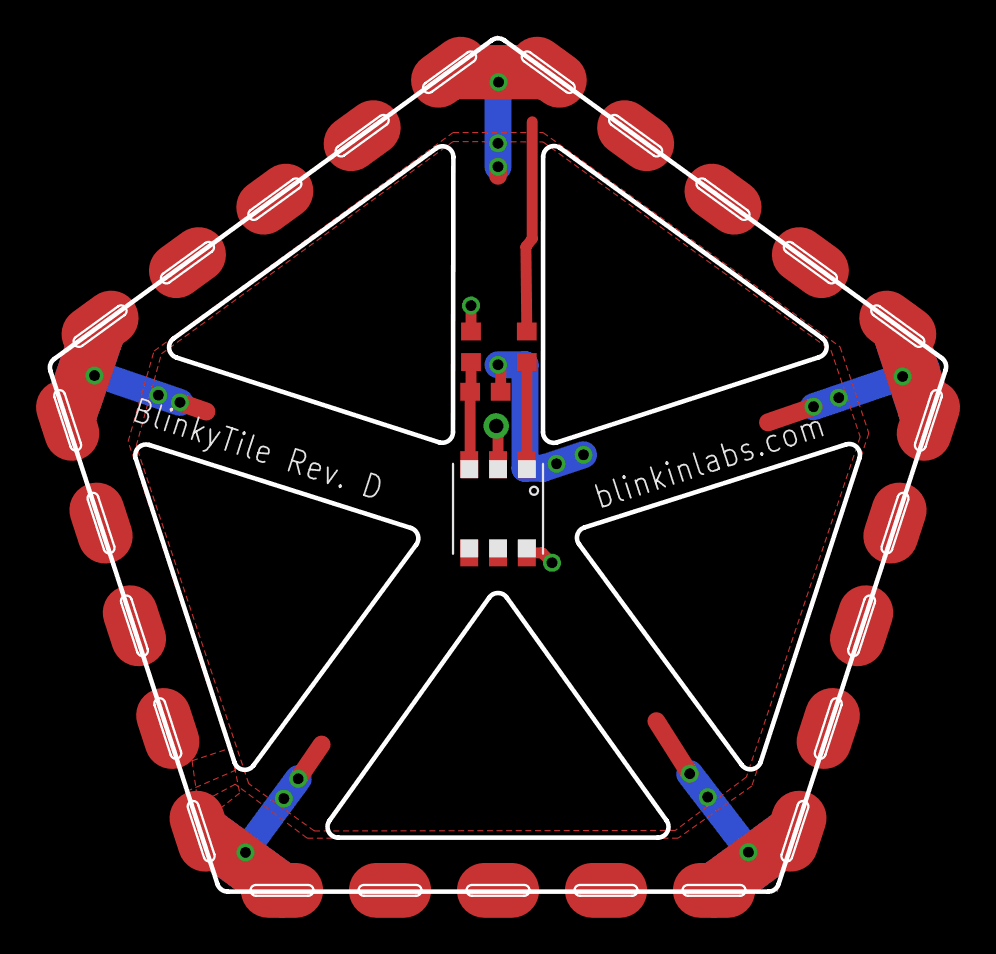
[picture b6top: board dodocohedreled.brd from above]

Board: 2 copper layers, 49.8 x 47.6 mm, 9 parts (0 on the bottom side), 5 nets.

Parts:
C1: .1uF; C0603
R1: 75; R0603
R2: 10k; R0603
U$2, U$3, U$4, U$5, U$6: D_EDGESLOT; D_EDGE_SLOT
U$7: WS2822S_LED

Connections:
5V: R1.1, U$2.P$2, U$2.P$4, U$2.P$7, U$2.P$9, U$3.P$2, U$3.P$4, U$3.P$7, U$3.P$9, U$4.P$2, U$4.P$4, U$4.P$7, U$4.P$9, U$5.P$2, U$5.P$4, U$5.P$7, U$5.P$9, U$6.P$2, U$6.P$4, U$6.P$7, U$6.P$9, U$7.6
DATA: R2.2, U$2.P$3, U$2.P$8, U$3.P$3, U$3.P$8, U$4.P$3, U$4.P$8, U$5.P$3, U$5.P$8, U$6.P$3, U$6.P$8
GND: C1.2, U$2.P$1, U$2.P$5, U$2.P$6, U$2.P$10, U$3.P$1, U$3.P$5, U$3.P$6, U$3.P$10, U$4.P$1, U$4.P$5, U$4.P$6, U$4.P$10, U$5.P$1, U$5.P$5, U$5.P$6, U$5.P$10, U$6.P$1, U$6.P$5, U$6.P$6, U$6.P$10, U$7.4
unnamed: C1.1, R1.2, U$7.3
unnamed: R2.1, U$7.1

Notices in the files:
parts and their libraries:
SparkFun-Aesthetics: Licensing: CC v3.0 Share-Alike You are welcome to use this library for commercial purposes.
SparkFun-Aesthetics: Licensing: Creative Commons ShareAlike 4.0 International - https://creativecommons.org/licenses/by-sa/4.0
